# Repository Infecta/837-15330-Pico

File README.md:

> [!WARNING]
>
> This repo is still a work-in-progress state
>
> Some things might be missing until I can finish up on my side.

# slidrr-PSoC / 837-15330-Pico
An attempt at a recreation of the official CHUNITHM Ground Slider for home use.

This project aims to use the same hardware* and firmware of the real ground slider for a more accurate and _faithful_ recreation of CHUNITHM's ground slider input.

<sub>*Same PSoCs. LED driver, power management and other things are ignored.</sub>

**Why?**
---
It all started because I couldn't get a _thick_ (3mm) acrylic overlay working on my original [simpl-slidrr](https://github.com/infecta/simpl-slidrr) project simply due to the fact that the MPR121s perform badly on any overlay above 2mm in thickness.

With this project, since we are using the same PSoCs as the official ground slider it gives us the following benefits:

- As close as possible touch polling/scanning to match arcade
- Thick overlays work reliably (Tested with loose/unscrewed 3mm and 6mm briefly)
- No guesswork needed for psoc firmware

**What this project includes**
---
- KiCad Source Files for the PCB
- CAD Files for the case including the Fusion360 project
- Firmware for the RP2040 Zero

> [!WARNING]
>
> **Agentic AI usage disclosure**
>
> A huge chunk of the code was provided by an AI agent. This only applies to the firmware for the RP2040 Zero.
>
> You may experience weird issues, whacky edge cases that might happen.

**Hardware Architecture**
---
The main CY8C22345 communicates to the RP2040 through UART. The firmware will pass those commands transparently unless it's an LED packet in which case, will be parsed by the RP2040 itself to drive the LEDs   

To put it in simple terms, the main job of the RP2040 is a Serial to USB adapter*

<sub>_*If we just gloss over the fact it also does air tower and IO4 emulation_</sub>

```mermaid
graph LR;
CY(Main CY8C22345)
PICO(RP2040)
LEDS(SK6812MINI-E Array)
Q{IS IT AN LED PACKET}

HOST --> PICO
PICO --> Q
Q --> |NO| CY
Q --> |YES|LED(Parse LED Data) --> LEDS

```
<sup>_Very simplified flowchart of what it does._</sup>

## Parts Needed (PCB)
<sub>All SMD components are 0603 unless stated otherwise</sub>
| Item | Quantity | Notes |
|-|-|-|
| CY8C22345 | 2 | [Link(Taobao)](https://item.taobao.com/item.htm?app=firefox&bxsign=scd9rOtEH5153mIeRH7GMPgw3-ES263TqwWZAUW9XdXCYrmNxd8LlLLmxuiTGIFg5Yr0s1BOR5-z54nxIae25Bysl0wQ_QsDgy9YGaOTnT1PLHMj1ds6YtYJkS3Nt2SaPQEnqRAZ1HRSVvh9NfvvPF8rQ&cpp=1&id=972956170652&price=5.8). Same chips used as the official ground slider. Depending on where you are, these may be easier or harder to source. Must be an SSOP-28 package to fit on the PCB. If you found a different package you'll have modify the PCB. Get extras just in case things go wrong (bad chip, broken pins etc.)
| Arduino Pro Micro | 1 | A cheap (and slightly difficult) way to flash the PSoC with the ground slider firmware using [arduino_hssp](https://github.com/miracoli/arduino_hssp). **Make sure it's the 5V model**. **NOTE: You will need linux to use this with [psocdude](https://github.com/miracoli/psocdude)**. If you have another way of programming the PSoC like a MiniProg then go that route.
| WaveShare RP2040 Zero | 1 | Main brains (UART Passthrough, IO4, LED driver)
| [This](./guide-media/button.png) SMD tactile switch | 2 | I'm not sure what these are formally called. but I used these for the footprint on the PCB.
| SN74LV1T34DBVR Logic Level Shifter | 1 | This is for the SK6812MINI-E LED data pins (Needs 5V logic rather than 3.3V logic). You can substitute this with any other level shifter provided it's pin compatible or modify the PCB if you want to use a different one.
| SK6812MINI-E LEDs | 31 | LEDs.
| 4x DIP switch | 1 | Temporary but needed during flashing & troubleshooting. Mainly to connect both PSoC I<sup>2</sup>C lines and connect to the I<sup>2</sup>C pull-up resistors.
| JST XH5 Connectors | 2 | Optional. But nice to have to reliably flash PSoCs
| JST XH6 Connectors | 2 | For connecting air towers
| 100nf/0.1uF X5R Capacitors | 32 | Decoupling caps for level shifter and LEDs 
| 4.7uF X5R Capacitors | 4 | Decoupling caps for PSoCs
| 4.7nF X7R Capacitors | 2 | CapSense<sup>TM</sup> Modulator cap
| 560R/560ohm Resistors | 32 | Placed before the touch electrodes. Values are just an estimate and typical range I have tested.
| 1K Resistor | 1 | Part of a voltage divider to shift down the 5V UART signal to 3.3V going into the RP2040 Zero
| 2K Resistor | 1 | Part of a voltage divider to shift down the 5V UART signal to 3.3V going into the RP2040 Zero
| 3K - 4.7K Resistor | 2 | I<sup>2</sup>C pull-up resistors. Within this range should be fine.
| 330R/330ohm Resistor | 1 | Needed for the logic level shifter. Followed datasheet. If changing level shifter check datasheet for info.
| [whowechina chu_pico IR airs](https://github.com/whowechina/chu_pico) | 1 pair | IR tower code based around this design. Check chu_pico repo for more info. **IMPORTANT:** CURRENT LIMITING RESISTORS NEED TO BE CHANGED TO A HIGHER VALUE. CHECK BELOW.

## Notes

> [!WARNING]
>
> If you have fabricated a PCB before 11th October 2026; Bridge Pin 11 and 12 of U2's pins. I discovered the controller stopped working seemingly out of nowhere due to the floating UART pins on the 2nd PSoC. Huge thanks to @somewhatlurker from the Cons&Stuff discord for helping me troubleshoot this.
> 

The chu_pico airs draw too much power with 0.75ohm resistor (If we were to follow whowe's guide for the airs). Either due to the WaveShare RP2040 zero's 3v3 regulator or general power budget **it is too high** and there will not be enough power to go around.

> [!WARNING]
>
> Using the airs as-is with the 0.75ohm resistors **may** burn out the 3v3 regulator as it can get **very** hot.
> 

I suggest using a 50ohm or 100ohm resistor instead. You can almost use down to 10ohms, anything lower doesn't work.

## Build _*"guide"*_

This doc fully assumes you are comfortable with soldering SMD components.

_Protip: Use the Interactive Html Bom plugin on KiCAD to easily figure out where all the components go._

### Ordering the PCB
---
We're using [JLCPCB](https://jlcpcb.com) for this guide.

You can leave everything on default but I recommend a black solder mask so that the lights look better

### Notes for the RP2040-Zero
---
I won't lie, I forgot why I even placed the footprint they way I did.
But the RP2040 chip is facing **upwards** so please keep that in mind.

### Flashing the firmware
---
**This section will assume you are doing the psocdude + arduino_hssp route.**

**This also assumes you have sourced your own dump of the offical 837-15330/Ground slider firmware**

**This section will not guide you on how to flash the arduino or compile psocdude. Use google or ask an LLM for guidance.**

Few things are needed to change in the `psocdude.conf` file in order to get it flashed.

Inside `psocdude.conf` find the `CY8C22345` line. It should look like this.
```bash
#------------------------------------------------------------
# CY8C22345
#------------------------------------------------------------

part
  id      = "CY8C22345";
  desc    = "CY8C22345";
  signature   = 0x00 0xD1;
  checksum_setup = CHECKSUM_SETUP_22_24_28_29_TST120_TMG120_TMA120;
  program_block = PROGRAM_BLOCK_21_22_23_24_28_29_TST_TMG_TMA;
  multi_bank = yes;
  memory "signature"
    size = 2;
  ;
;
```

Change it so it looks like this:
```bash
#------------------------------------------------------------
# CY8C22345
#------------------------------------------------------------

part
  id      = "CY8C22345";
  desc    = "CY8C22345";
  signature   = 0x00 0xD0;
  checksum_setup = CHECKSUM_SETUP_22_24_28_29_TST120_TMG120_TMA120;
  program_block = PROGRAM_BLOCK_21_22_23_24_28_29_TST_TMG_TMA;
  multi_bank = yes;
  memory "flash"
    paged     = yes;
    size      = 16384;
    page_size = 64;
    num_pages = 256;
    blocksize = 64;
    readsize  = 64;
  ;
  memory "signature"
    size = 2;
  ;
;
```

Flash the PSoC with:
```bash
psocdude -C psocdude.conf -p CY8C22345 -c arduino -P /dev/ttyACM0 -b 115200 -U flash:w:<DUMPED_FIRMWARE.bin/.hex>:r -F
```

#### Troubleshooting
---

**Scenario 1**

If your output looks like this:
```bash
Reading |                     | 0% 0.00spsocdude: ser_recv(): proggrammer is not responding
psocdude: error reading signature data for part "CY8C22345", rc=-1
psocdude: error reading signature data, rc=-1
```

It could be either one of 2 issues:

1. Unplug and replug your programmer, then try running the command again.

2. If that doesn't work check your solder connections.

**Scenario 2**

If your signature is 0xffff
1. Bad soldering.
2. Bad chip. (Unconfirmed)

I haven't figured out why this happens as of writing this. My only solution was switching out the chips with the extras I already had.

There might be more issues that I haven't experienced yet so I can't cover all bases.

### Case
---
TODO: CASE GUIDE HERE

## Credits

[whowechina](https://github.com/whowechina) - Air Code and PCB is heavily referenced and adapted for the firmware from the [chu_pico](https://github.com/whowechina/chu_pico) project.

[Cons&Stuff](https://consandstuff.github.io/) Discord Server - For guidance and troubleshooting of my project especially [somewhatlurker](https://github.com/somewhatlurker) for their insight of the slider protocol.

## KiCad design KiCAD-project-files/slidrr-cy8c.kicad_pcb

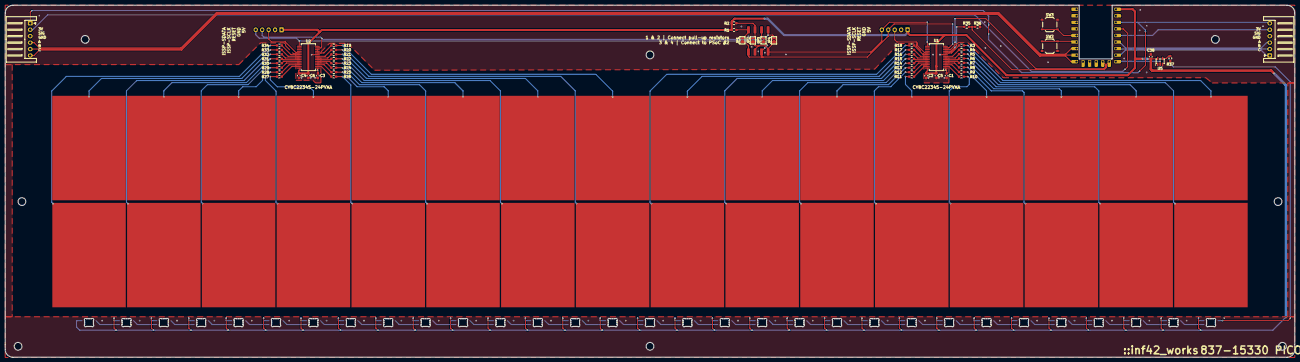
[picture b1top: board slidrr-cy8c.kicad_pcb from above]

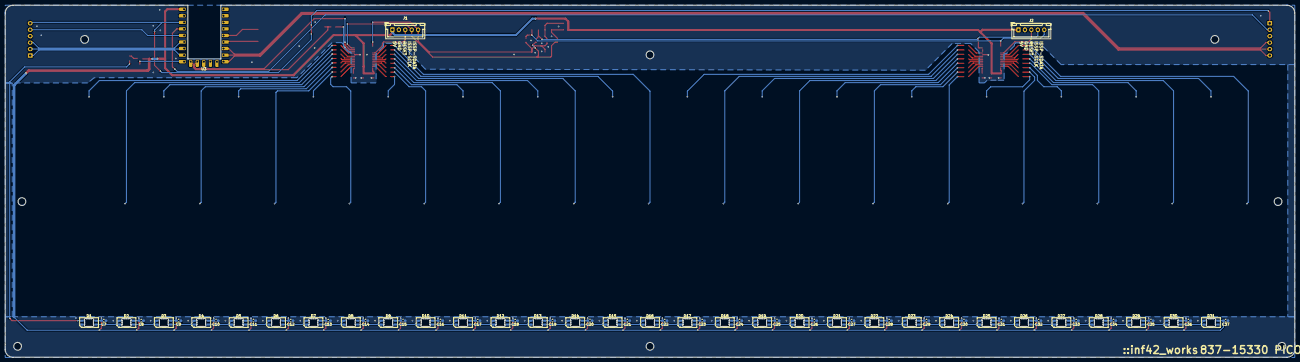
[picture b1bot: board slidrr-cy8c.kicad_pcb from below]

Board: 2 copper layers, 500.0 x 136.5 mm, 122 parts (65 on the bottom side), 123 nets.

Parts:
C1, C3: 4.7nF X7R / 2.2nF X7R; C_0603_1608Metric_Pad1.08x0.95mm_HandSolder
C2, C4, C5, C6: X5R 4.7uF 16V; C_0603_1608Metric_Pad1.08x0.95mm_HandSolder
C7, C8, C9, C10, C11, C12, C13, C14, C15, C16, C17, C18, C19, C20, C21, C22, C23, C24, C25, C26, C27, C28, C29, C30, C31, C32, C33, C34, C35, C36, C37, C38: 0.1uF; C_0603_1608Metric_Pad1.08x0.95mm_HandSolder
D1, D2, D3, D4, D5, D6, D7, D8, D9, D10, D11, D12, D13, D14, D15, D16, D17, D18, D19, D20, D21, D22, D23, D24, D25, D26, D27, D28, D29, D30, D31: SK6812MINI-E; LED_SK6812MINI-E_3.2x2.8mm_P1.5mm_ReverseMount
J1: ISSP U1; JST_XH_B5B-XH-A_1x05_P2.50mm_Vertical
J2: ISSP U2; JST_XH_B5B-XH-A_1x05_P2.50mm_Vertical
J3: Conn_01x32_Socket; slidrr-touchslider
J4, J5: JST-XH Series; JST_XH_S6B-XH-A_1x06_P2.50mm_Horizontal
JP1: SW1; SolderJumper-2_P1.3mm_Open_TrianglePad1.0x1.5mm
JP2: SW2; SolderJumper-2_P1.3mm_Open_TrianglePad1.0x1.5mm
JP3: SW3; SolderJumper-2_P1.3mm_Open_TrianglePad1.0x1.5mm
JP4: SW4; SolderJumper-2_P1.3mm_Open_TrianglePad1.0x1.5mm
R1, R2: 3.2K; R_0603_1608Metric_Pad0.98x0.95mm_HandSolder
R3, R4, R5, R6, R7, R8, R9, R10, R11, R12, R13, R14, R15, R16, R17, R18, R19, R20, R21, R22, R23, R24, R25, R26, R27, R28, R29, R30, R31, R32, R33, R34: 560R; R_0603_1608Metric_Pad0.98x0.95mm_HandSolder
R35: 1K; R_0603_1608Metric_Pad0.98x0.95mm_HandSolder
R36: 2K; R_0603_1608Metric_Pad0.98x0.95mm_HandSolder
R37: 330R; R_0603_1608Metric_Pad0.98x0.95mm_HandSolder
SW1: SW_DIP_x04; SW_DIP_SPSTx04_Slide_9.78x12.34mm_W8.61mm_P2.54mm
SW2, SW3: SW_Push; SW_Push_1P1T_XKB_TS-1187A
U1, U2: SSOP-28_5.3x10.2mm_P0.65mm
U3: RP2040-Zero
U5: SN74LV1T34DBVR; SOT-23-5

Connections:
3V3: J4.1, J5.6, U3.20 (3V3)
3v3 LED DATA: U3.14 (GP14), U5.2 (A)
5V LED DATA: D1.2 (DIN), R37.2
+5V: C2.1, C4.1, C5.1, C6.1, C7.2, C8.2, C9.2, C10.2, C11.2, C12.2, C13.2, C14.2, C15.2, C16.2, C17.2, C18.2, C19.2, C20.2, C21.2, C22.2, C23.2, C24.2, C25.2, C26.2, C27.2, C28.2, C29.2, C30.2, C31.2, C32.2, C33.2, C34.2, C35.2, C36.2, C37.2, C38.2, D1.3 (VDD), D2.3 (VDD), D3.3 (VDD), D4.3 (VDD), D5.3 (VDD), D6.3 (VDD), D7.3 (VDD), D8.3 (VDD), D9.3 (VDD), D10.3 (VDD), D11.3 (VDD), D12.3 (VDD), D13.3 (VDD), D14.3 (VDD), D15.3 (VDD), D16.3 (VDD), D17.3 (VDD), D18.3 (VDD), D19.3 (VDD), D20.3 (VDD), D21.3 (VDD), D22.3 (VDD), D23.3 (VDD), D24.3 (VDD), D25.3 (VDD), D26.3 (VDD), D27.3 (VDD), D28.3 (VDD), D29.3 (VDD), D30.3 (VDD), D31.3 (VDD), J1.1, J2.1, R1.2, R2.2, U1.28 (Vdd), U2.28 (Vdd), U3.22 (5V), U5.5 (VCC)
AIR A L: J4.4, U3.6 (GP6)
AIR A R: J5.3, U3.17 (GP27)
AIR B L: J4.5, U3.7 (GP7)
AIR B R: J5.2, U3.16 (GP26)
AIR C L: J4.6, U3.8 (GP8)
AIR C R: J5.1, U3.15 (GP15)
AIR SIG L: J4.2, U3.19 (GP29)
AIR SIG R: J5.5, U3.18 (GP28)
GND: C1.1, C2.2, C3.1, C4.2, C5.2, C6.2, C7.1, C8.1, C9.1, C10.1, C11.1, C12.1, C13.1, C14.1, C15.1, C16.1, C17.1, C18.1, C19.1, C20.1, C21.1, C22.1, C23.1, C24.1, C25.1, C26.1, C27.1, C28.1, C29.1, C30.1, C31.1, C32.1, C33.1, C34.1, C35.1, C36.1, C37.1, C38.1, D1.1 (VSS), D2.1 (VSS), D3.1 (VSS), D4.1 (VSS), D5.1 (VSS), D6.1 (VSS), D7.1 (VSS), D8.1 (VSS), D9.1 (VSS), D10.1 (VSS), D11.1 (VSS), D12.1 (VSS), D13.1 (VSS), D14.1 (VSS), D15.1 (VSS), D16.1 (VSS), D17.1 (VSS), D18.1 (VSS), D19.1 (VSS), D20.1 (VSS), D21.1 (VSS), D22.1 (VSS), D23.1 (VSS), D24.1 (VSS), D25.1 (VSS), D26.1 (VSS), D27.1 (VSS), D28.1 (VSS), D29.1 (VSS), D30.1 (VSS), D31.1 (VSS), J1.2, J2.2, J4.3, J5.4, R36.2, SW2.2, SW3.2, U1.9 (Vss/GND), U1.14 (Vss/GND), U2.9 (Vss/GND), U2.14 (Vss/GND), U3.21 (GND), U5.3 (GND)
I2C_SCL_U1: J1.4, JP1.1 (A), JP3.1 (A), SW1.1, SW1.3, U1.13 (P1[1])
I2C_SCL_U2: J2.4, JP3.2 (B), SW1.6, U2.13 (P1[1])
I2C_SDA_U1: J1.5, JP2.1 (A), JP4.1 (A), SW1.2, SW1.4, U1.15 (P1[0])
I2C_SDA_U2: J2.5, JP4.2 (B), SW1.5, U2.15 (P1[0])
ISSP_RESET_U1: J1.3, U1.19 (XRES)
ISSP_RESET_U2: J2.3, U2.19 (XRES)
unnamed: D1.4 (DOUT), D2.2 (DIN)
unnamed: D2.4 (DOUT), D3.2 (DIN)
unnamed: D3.4 (DOUT), D4.2 (DIN)
unnamed: D4.4 (DOUT), D5.2 (DIN)
unnamed: D5.4 (DOUT), D6.2 (DIN)
unnamed: D6.4 (DOUT), D7.2 (DIN)
unnamed: D7.4 (DOUT), D8.2 (DIN)
unnamed: D8.4 (DOUT), D9.2 (DIN)
unnamed: D9.4 (DOUT), D10.2 (DIN)
unnamed: D10.4 (DOUT), D11.2 (DIN)
unnamed: D11.4 (DOUT), D12.2 (DIN)
unnamed: D12.4 (DOUT), D13.2 (DIN)
unnamed: D13.4 (DOUT), D14.2 (DIN)
unnamed: D14.4 (DOUT), D15.2 (DIN)
unnamed: D15.4 (DOUT), D16.2 (DIN)
unnamed: D16.4 (DOUT), D17.2 (DIN)
unnamed: D17.4 (DOUT), D18.2 (DIN)
unnamed: D18.4 (DOUT), D19.2 (DIN)
unnamed: D19.4 (DOUT), D20.2 (DIN)
unnamed: D20.4 (DOUT), D21.2 (DIN)
unnamed: D21.4 (DOUT), D22.2 (DIN)
unnamed: D22.4 (DOUT), D23.2 (DIN)
unnamed: D23.4 (DOUT), D24.2 (DIN)
unnamed: D24.4 (DOUT), D25.2 (DIN)
unnamed: D25.4 (DOUT), D26.2 (DIN)
unnamed: D26.4 (DOUT), D27.2 (DIN)
unnamed: D27.4 (DOUT), D28.2 (DIN)
unnamed: D28.4 (DOUT), D29.2 (DIN)
unnamed: D29.4 (DOUT), D30.2 (DIN)
unnamed: D30.4 (DOUT), D31.2 (DIN)
unnamed: J3.1, R3.1
unnamed: J3.2, R4.1
unnamed: J3.3, R5.1
unnamed: J3.4, R6.1
unnamed: J3.5, R7.1
unnamed: J3.6, R8.1
unnamed: J3.7, R9.1
unnamed: J3.8, R10.1
unnamed: J3.9, R11.1
unnamed: J3.10, R12.1
unnamed: J3.11, R13.1
unnamed: J3.12, R14.1
unnamed: J3.13, R15.1
unnamed: J3.14, R16.1
unnamed: J3.15, R17.1
unnamed: J3.16, R18.1
unnamed: J3.17, R19.1
unnamed: J3.18, R20.1
unnamed: J3.19, R21.1
unnamed: J3.20, R22.1
unnamed: J3.21, R23.1
unnamed: J3.22, R24.1
unnamed: J3.23, R25.1
unnamed: J3.24, R26.1
unnamed: J3.25, R27.1
unnamed: J3.26, R28.1
unnamed: J3.27, R29.1
unnamed: J3.28, R30.1
unnamed: J3.29, R31.1
unnamed: J3.30, R32.1
unnamed: J3.31, R33.1
unnamed: J3.32, R34.1
unnamed: JP1.2 (B), R1.1, SW1.8
unnamed: JP2.2 (B), R2.1, SW1.7
unnamed: C1.2, U1.1 (P0[7])
unnamed: R35.2, R36.1, U3.13 (GP13)
unnamed: R37.1, U5.4 (Y)
SERVICE: SW2.1, U3.5 (GP5)
TEST: SW3.1, U3.4 (GP4)
TOUCH 1: R3.2, U1.10 (P1[7])
TOUCH 2: R4.2, U1.8 (P2[1])
TOUCH 3: R5.2, U1.7 (P2[3])
TOUCH 4: R6.2, U1.6 (P2[5])
TOUCH 5: R7.2, U1.5 (P2[7])
TOUCH 6: R8.2, U1.4 (P0[1])
TOUCH 7: R9.2, U1.3 (P0[3])
TOUCH 8: R10.2, U1.2 (P0[5])
TOUCH 9: R11.2, U1.27 (P0[6])
TOUCH 10: R12.2, U1.26 (P0[4])
TOUCH 11: R13.2, U1.25 (P0[2])
TOUCH 12: R14.2, U1.24 (P0[0])
TOUCH 13: R15.2, U1.23 (P2[6])
TOUCH 14: R16.2, U1.22 (P2[4])
TOUCH 15: R17.2, U1.21 (P2[2])
TOUCH 16: R18.2, U1.20 (P2[0])
TOUCH 17: R19.2, U2.10 (P1[7])
TOUCH 18: R20.2, U2.8 (P2[1])
TOUCH 19: R21.2, U2.7 (P2[3])
TOUCH 20: R22.2, U2.6 (P2[5])
TOUCH 21: R23.2, U2.5 (P2[7])
TOUCH 22: R24.2, U2.4 (P0[1])
TOUCH 23: R25.2, U2.3 (P0[3])
TOUCH 24: R26.2, U2.2 (P0[5])
TOUCH 25: R27.2, U2.27 (P0[6])
TOUCH 26: R28.2, U2.26 (P0[4])
TOUCH 27: R29.2, U2.25 (P0[2])
TOUCH 28: R30.2, U2.24 (P0[0])
TOUCH 29: R31.2, U2.23 (P2[6])
TOUCH 30: R32.2, U2.22 (P2[4])
TOUCH 31: R33.2, U2.21 (P2[2])
TOUCH 32: R34.2, U2.20 (P2[0])
U2_UART_BRIDGE: U2.11 (P1[5]), U2.12 (P1[3])
UART_RX_U1: U1.12 (P1[3]), U3.12 (GP12)
UART_TX_U1: R35.1, U1.11 (P1[5])
